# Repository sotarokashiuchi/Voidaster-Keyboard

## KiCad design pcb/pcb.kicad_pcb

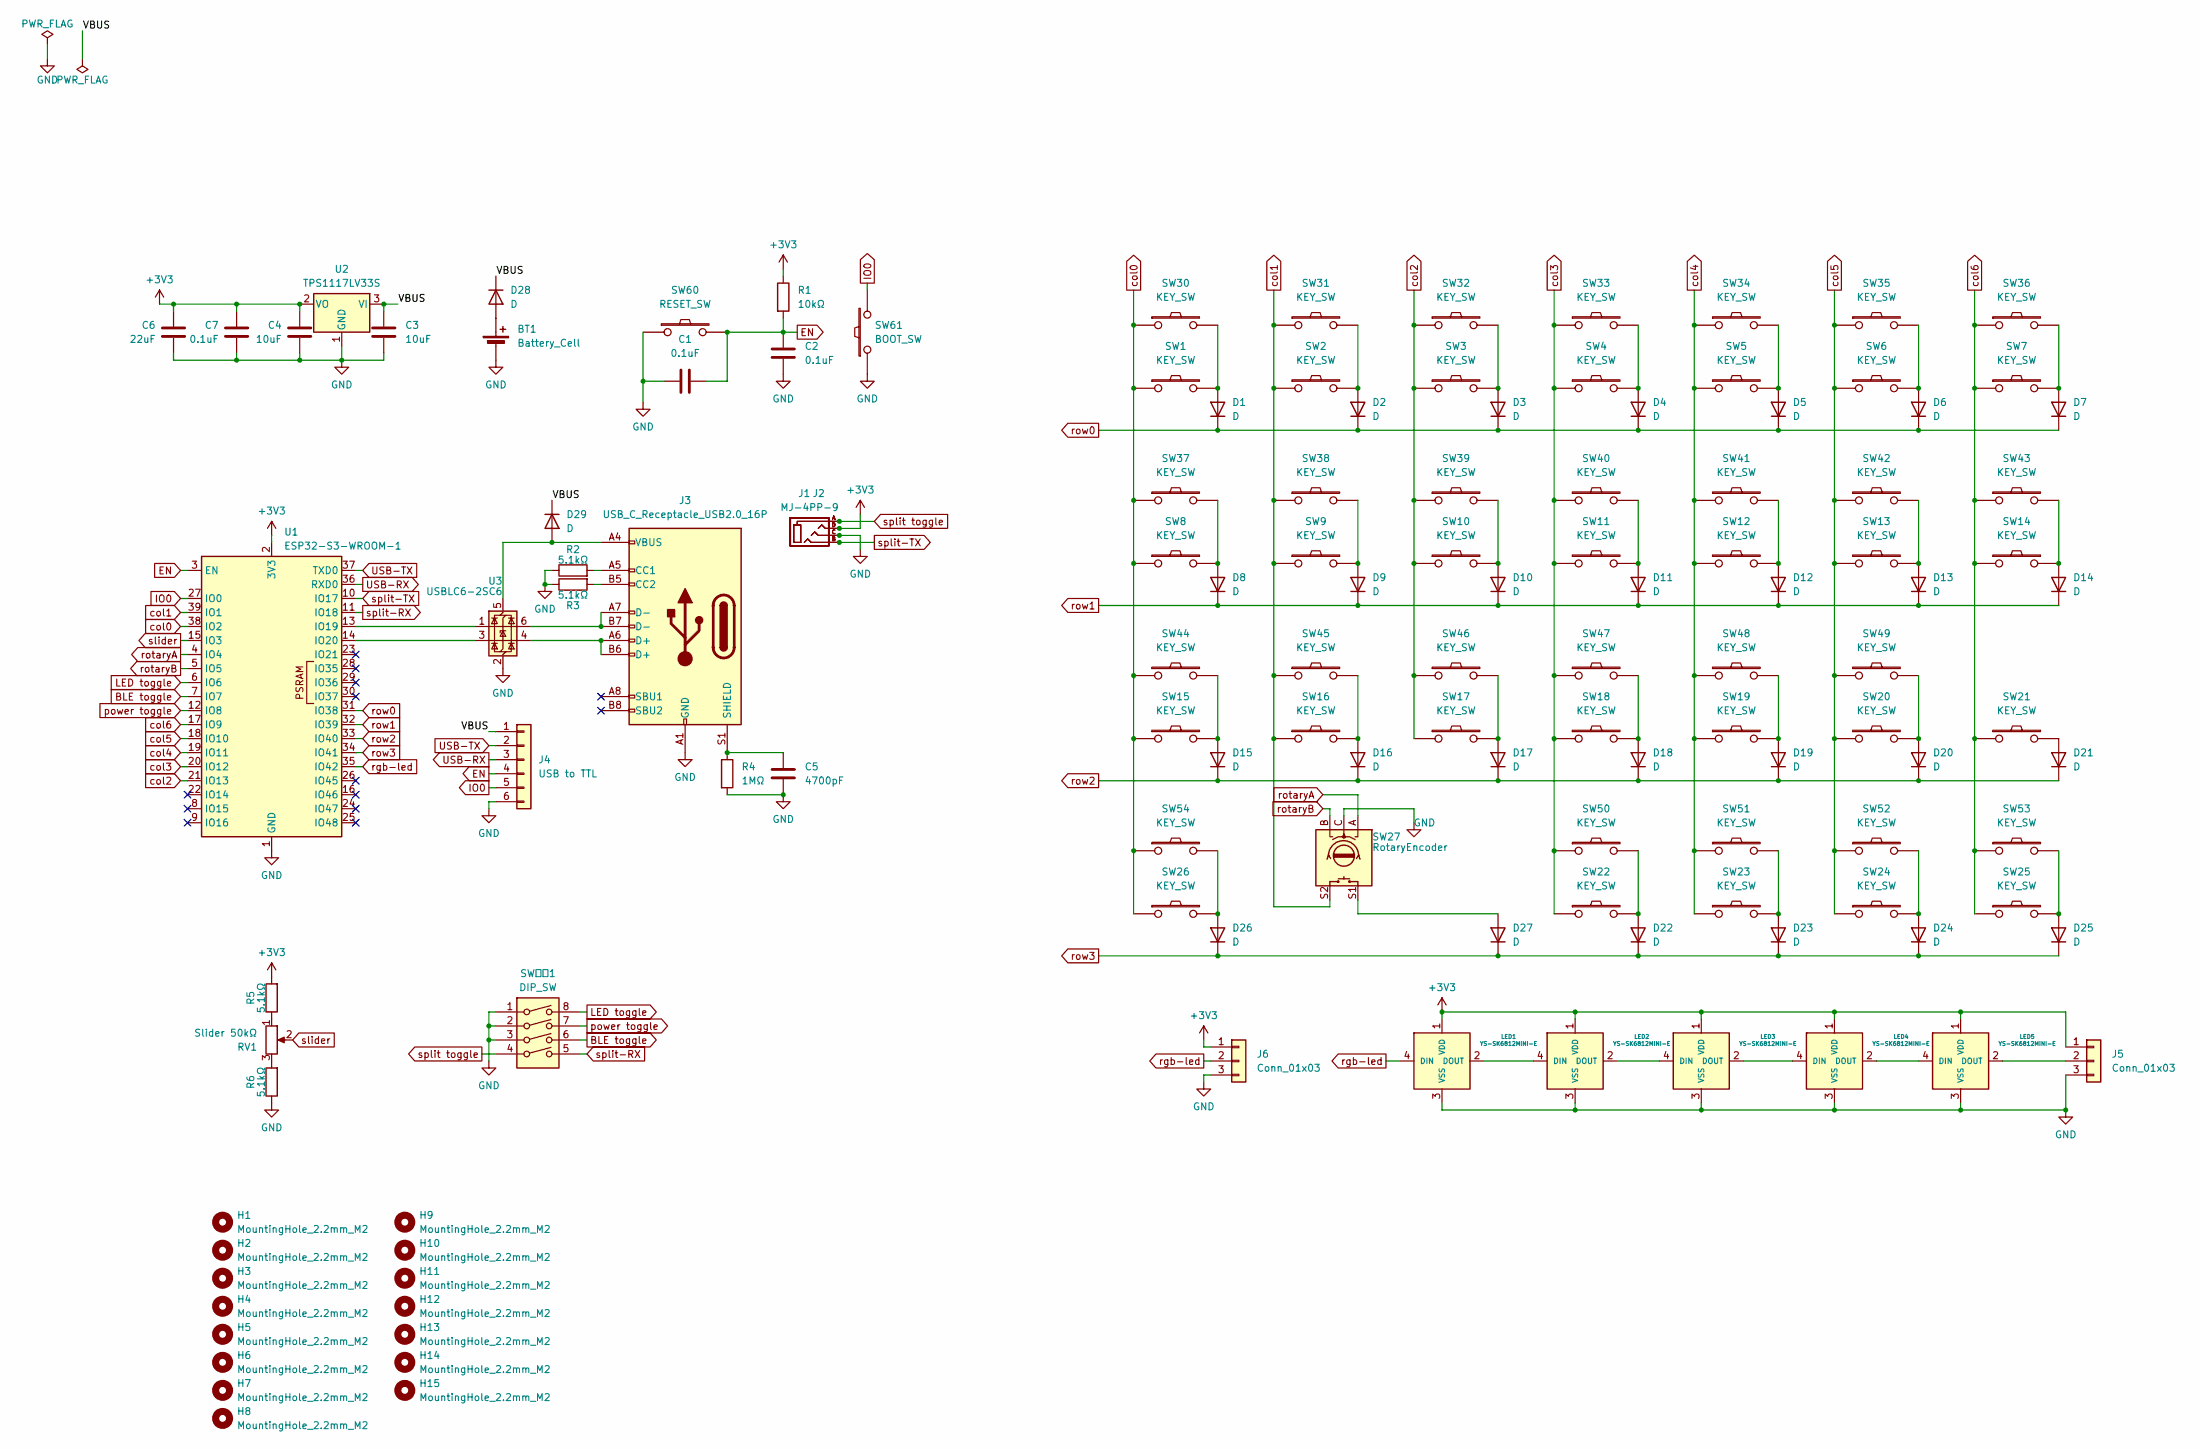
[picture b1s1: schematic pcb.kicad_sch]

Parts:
BT1: Battery_Cell; JST_XH_S2B-XH-A_1x02_P2.50mm_Horizontal
C1, C2: 0.1uF; C_0805_2012Metric_Pad1.18x1.45mm_HandSolder_rev
C3, C4: 10uF; C_0805_2012Metric_Pad1.18x1.45mm_HandSolder
C5: 4700pF; C_0603_1608Metric_Pad1.08x0.95mm_HandSolder
C6: 22uF; C_0805_2012Metric_Pad1.18x1.45mm_HandSolder
C7: 0.1uF; C_0805_2012Metric_Pad1.18x1.45mm_HandSolder
D1, D2, D3, D4, D5, D6, D7, D8, D9, D10, D11, D12, D13, D14, D15, D16, D17, D18, D19, D20, D21, D22, D23, D24, D25, D26, D27, D28, D29: D; Diode-dual
H1, H2, H3, H4, H5, H6, H7, H8, H9, H10, H11, H12, H13, H14, H15: MountingHole_2.2mm_M2
J1, J2: MJ-4PP-9
J3: USB_C_Receptacle_USB2.0_16P; USB_C_Receptacle_GCT_USB4105-xx-A_16P_TopMnt_Horizontal_rev
J4: USB to TTL; PinSocket_1x06_P2.54mm_Horizontal
J5, J6: Conn_01x03; StripLED_rev
LED1, LED2, LED3, LED4, LED5: YS-SK6812MINI-E
R1: 10kΩ; Resistor-Hybrid
R2, R3: 5.1kΩ; Resistor-Hybrid_rev
R4: 1MΩ; Resistor-Hybrid_rev
R5, R6: 5.1kΩ; Resistor-Hybrid
RV1: Slider 50kΩ; SL4515NB103L15CM
SW1, SW2, SW3, SW4, SW5, SW6, SW7, SW15, SW16, SW17, SW18, SW19, SW20, SW21, SW30, SW31, SW32, SW33, SW34, SW35, SW36, SW37, SW38, SW39, SW40, SW41, SW42, SW43, SW44, SW45, SW46, SW47, SW48, SW49, SW50, SW51, SW52, SW53, SW54: KEY_SW; keyswitch_cherrymx_hotswap_1u
SW8, SW9, SW10, SW11, SW12, SW13, SW14, SW22, SW23, SW24, SW25, SW26: KEY_SW; keyswitch_cherrymx_hotswap_1u_no_hole
SW27: RotaryEncoder; RotaryEncoder_EC11
SW60: RESET_SW; ResetSW
SW61: BOOT_SW; ResetSW
SW６２1: DIP_SW; DIPS762W80P254L1170H690Q8N
U1: ESP32-S3-WROOM-1
U2: TPS1117LV33S; SOT-223-3_TabPin2
U3: USBLC6-2SC6; SOT-23-6

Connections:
+3V3: C4.1, C6.1, C7.1, J1.D, J2.D, J5.1, J6.1, LED1.1 (VDD), LED2.1 (VDD), LED3.1 (VDD), LED4.1 (VDD), LED5.1 (VDD), R1.1, R5.2, U1.2 (3V3), U2.2 (VO)
/VBUS: C3.1, D28.1 (K), D29.1 (K), J4.1, U2.3 (VI)
BLE toggle: SW６２1.6, U1.7 (IO7)
EN: C1.2, C2.2, J4.4, R1.2, SW60.2, U1.3 (EN)
GND: BT1.2 (-), C1.1, C2.1, C3.2, C4.2, C5.2, C6.2, C7.2, J1.C, J2.C, J3.A1 (GND), J3.A12 (GND), J3.B1 (GND), J3.B12 (GND), J4.6, J5.3, J6.3, LED1.3 (VSS), LED2.3 (VSS), LED3.3 (VSS), LED4.3 (VSS), LED5.3 (VSS), R2.1, R3.1, R4.2, R6.1, SW27.C, SW60.1, SW61.1, SW６２1.1, SW６２1.2, SW６２1.3, U1.1 (GND), U1.40 (GND), U1.41 (GND), U2.1 (GND), U3.2 (GND)
IO0: J4.5, SW61.2, U1.27 (IO0)
LED toggle: SW６２1.8, U1.6 (IO6)
unnamed: BT1.1 (+), D28.2 (A)
unnamed: D1.2 (A), SW1.2, SW30.2
unnamed: D2.2 (A), SW2.2, SW31.2
unnamed: D3.2 (A), SW3.2, SW32.2
unnamed: D4.2 (A), SW4.2, SW33.2
unnamed: D5.2 (A), SW5.2, SW34.2
unnamed: D6.2 (A), SW6.2, SW35.2
unnamed: D7.2 (A), SW7.2, SW36.2
unnamed: D8.2 (A), SW8.2, SW37.2
unnamed: D9.2 (A), SW9.2, SW38.2
unnamed: D10.2 (A), SW10.2, SW39.2
unnamed: D11.2 (A), SW11.2, SW40.2
unnamed: D12.2 (A), SW12.2, SW41.2
unnamed: D13.2 (A), SW13.2, SW42.2
unnamed: D14.2 (A), SW14.2, SW43.2
unnamed: D15.2 (A), SW15.2, SW44.2
unnamed: D16.2 (A), SW16.2, SW45.2
unnamed: D17.2 (A), SW17.2, SW46.2
unnamed: D18.2 (A), SW18.2, SW47.2
unnamed: D19.2 (A), SW19.2, SW48.2
unnamed: D20.2 (A), SW20.2, SW49.2
unnamed: D21.2 (A), SW21.2
unnamed: D22.2 (A), SW22.2, SW50.2
unnamed: D23.2 (A), SW23.2, SW51.2
unnamed: D24.2 (A), SW24.2, SW52.2
unnamed: D25.2 (A), SW25.2, SW53.2
unnamed: D26.2 (A), SW26.2, SW54.2
unnamed: D27.2 (A), SW27.S1
unnamed: D29.2 (A), J3.A4 (VBUS), J3.A9 (VBUS), J3.B4 (VBUS), J3.B9 (VBUS), U3.5 (VBUS)
unnamed: J3.A5 (CC1), R2.2
unnamed: J3.B5 (CC2), R3.2
unnamed: J3.A6 (D+), J3.B6 (D+), U3.4 (I/O2)
unnamed: J3.A7 (D-), J3.B7 (D-), U3.6 (I/O1)
unnamed: C5.1, J3.S1 (SHIELD), R4.1
unnamed: J5.2, LED5.2 (DOUT)
unnamed: LED1.2 (DOUT), LED2.4 (DIN)
unnamed: LED2.2 (DOUT), LED3.4 (DIN)
unnamed: LED3.2 (DOUT), LED4.4 (DIN)
unnamed: LED4.2 (DOUT), LED5.4 (DIN)
unnamed: R5.1, RV1.1
unnamed: R6.2, RV1.3
unnamed: U1.13 (IO19), U3.1 (I/O1)
unnamed: U1.14 (IO20), U3.3 (I/O2)
USB-RX: J4.3, U1.36 (RXD0)
USB-TX: J4.2, U1.37 (TXD0)
col0: SW1.1, SW8.1, SW15.1, SW26.1, SW30.1, SW37.1, SW44.1, SW54.1, U1.38 (IO2)
col1: SW2.1, SW9.1, SW16.1, SW27.S2, SW31.1, SW38.1, SW45.1, U1.39 (IO1)
col2: SW3.1, SW10.1, SW17.1, SW32.1, SW39.1, SW46.1, U1.21 (IO13)
col3: SW4.1, SW11.1, SW18.1, SW22.1, SW33.1, SW40.1, SW47.1, SW50.1, U1.20 (IO12)
col4: SW5.1, SW12.1, SW19.1, SW23.1, SW34.1, SW41.1, SW48.1, SW51.1, U1.19 (IO11)
col5: SW6.1, SW13.1, SW20.1, SW24.1, SW35.1, SW42.1, SW49.1, SW52.1, U1.18 (IO10)
col6: SW7.1, SW14.1, SW21.1, SW25.1, SW36.1, SW43.1, SW53.1, U1.17 (IO9)
power toggle: SW６２1.7, U1.12 (IO8)
rgb-led: J6.2, LED1.4 (DIN), U1.35 (IO42)
rotaryA: SW27.A, U1.4 (IO4)
rotaryB: SW27.B, U1.5 (IO5)
row0: D1.1 (K), D2.1 (K), D3.1 (K), D4.1 (K), D5.1 (K), D6.1 (K), D7.1 (K), U1.31 (IO38)
row1: D8.1 (K), D9.1 (K), D10.1 (K), D11.1 (K), D12.1 (K), D13.1 (K), D14.1 (K), U1.32 (IO39)
row2: D15.1 (K), D16.1 (K), D17.1 (K), D18.1 (K), D19.1 (K), D20.1 (K), D21.1 (K), U1.33 (IO40)
row3: D22.1 (K), D23.1 (K), D24.1 (K), D25.1 (K), D26.1 (K), D27.1 (K), U1.34 (IO41)
slider: RV1.2, U1.15 (IO3)
split toggle: J1.A, J2.A, SW６２1.4
split-RX: SW６２1.5, U1.11 (IO18)
split-TX: J1.B, J2.B, U1.10 (IO17)

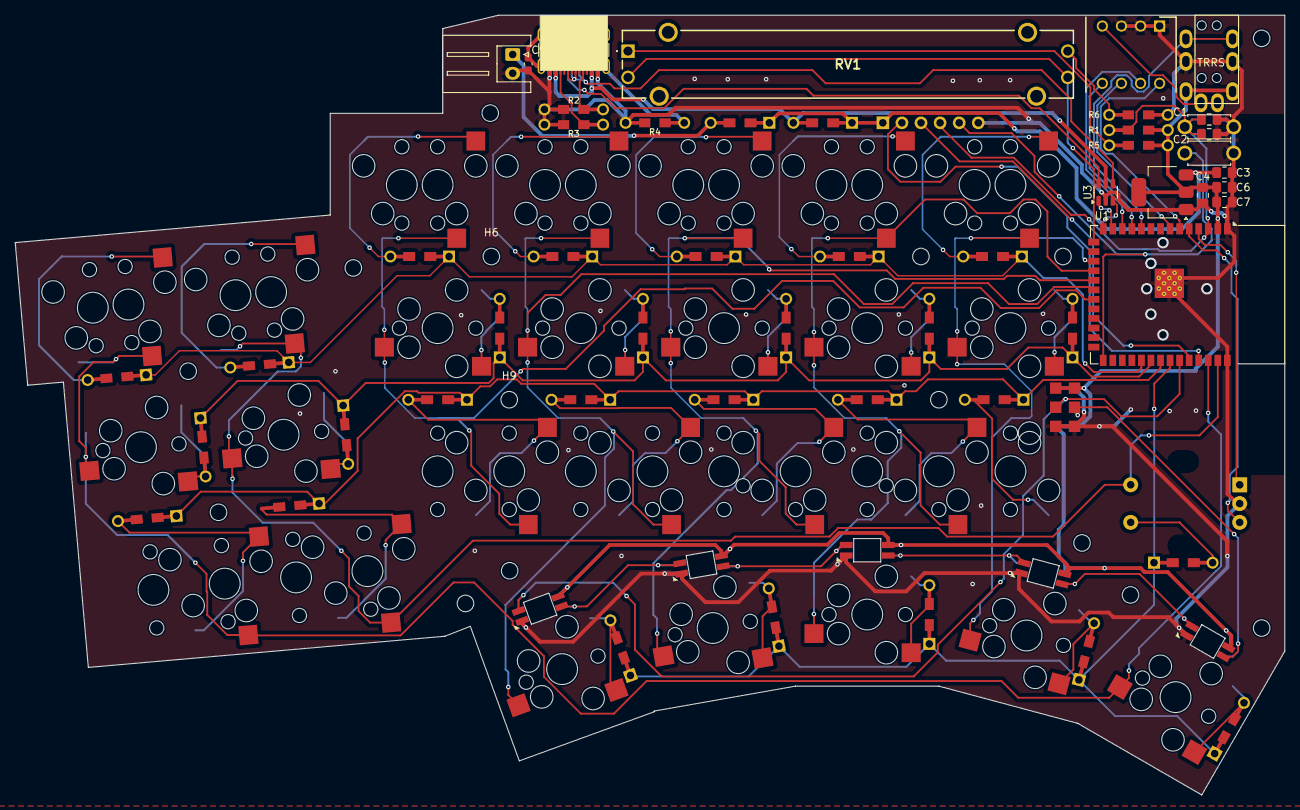
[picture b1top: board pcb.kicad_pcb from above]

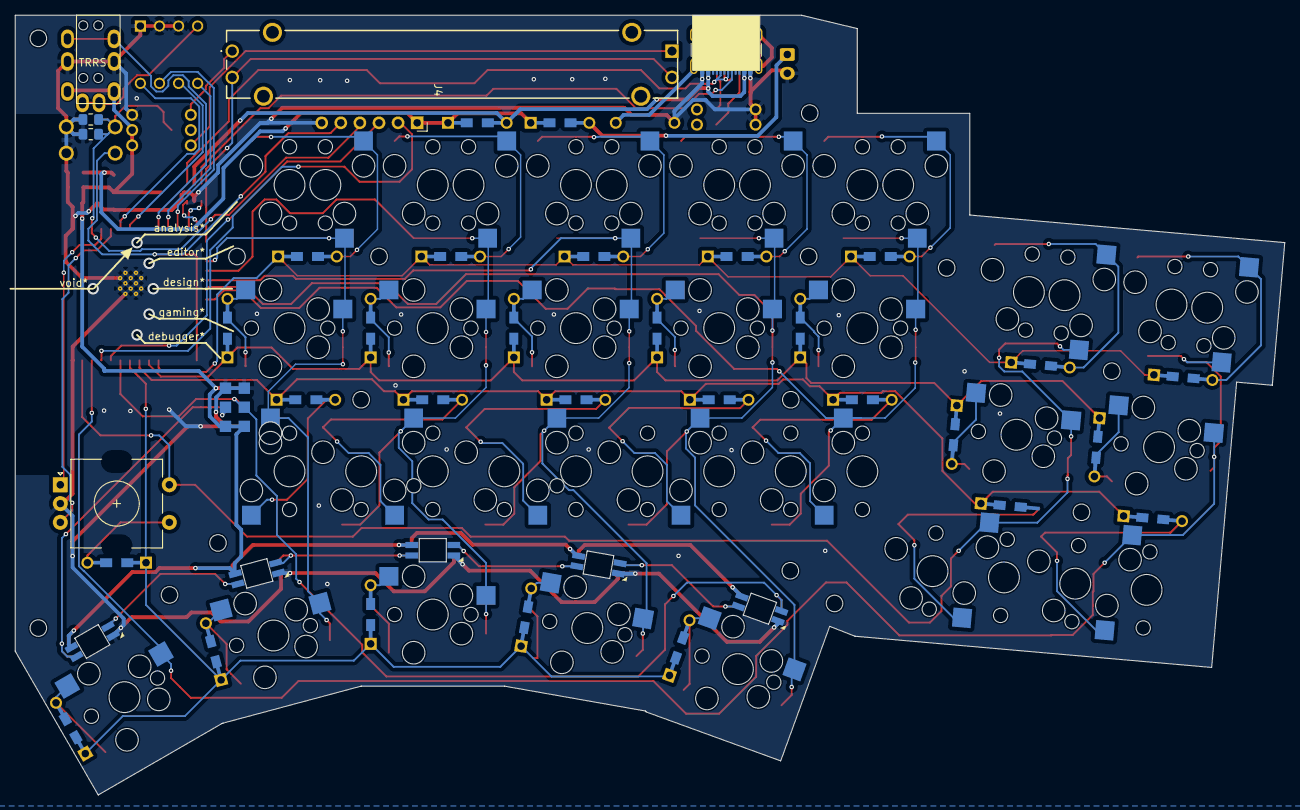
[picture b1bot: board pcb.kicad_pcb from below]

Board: 2 copper layers, 168.8 x 103.7 mm, 128 parts (29 on the bottom side), 71 nets.

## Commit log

2024-09-05 add library
2024-09-05 put symbols of sw and encoder
2024-09-05 link fotprint
2024-09-24 ESP32-S3-WROOM-1
2024-09-25 Boot Mode close #6
2024-09-26 USB type-C close #7
2024-09-26 split connector close #8
2024-09-28 pcb keyswitch
2024-09-28 USB to TTL close #9
2024-10-04 add lib
2024-10-04 DIP SW close #15
2024-10-04 slider close #13
2024-10-05 keyswitch and rotary encoder close #12
2024-10-05 battery close #10
2024-10-06 led close #14
2024-10-06 switch put to pcb
2024-10-09 ESP32 put to pcb
2024-10-11 connect
2024-10-12 fix DRC error of switch
2024-10-12 fix DRC error of LED
2024-10-12 put M2 hole
2024-10-13 completed ERC
2024-10-13 fix position of sch
2024-10-13 completed DRC
2024-10-14 logo
2024-10-14 put logo
2024-10-18 ortder pcb
2024-11-01 top case
2025-01-04 mini interrupt
2025-01-04 change to enum from define
2025-01-05 fix code
2025-01-05 fix enum
2025-01-06 loop
2025-01-07 change to pressRaw() from press()
2025-01-07 fix chattering
2025-01-07 change to array from list
2025-01-08 add layer
2025-01-08 split keyboard
2025-01-08 ファームウェアのベース部分 (#24)
    * loop
    * change to pressRaw() from press()
    * fix chattering
    * change to array from list
    * add layer
    * delete unusing include file
2025-01-19 add modeifiy key and alphabet
2025-03-14 add shifted-key
2025-08-28 Refactor key mapping and update layer handling in firmware. Changed key definitions to a more concise format, added a new SIGN layer, and improved key press/release logic for better functionality.
2025-08-28 Update README.md with new images and adjust image paths
2026-01-13 add alphabet at keytop
